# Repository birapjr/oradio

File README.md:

# oRadio
open all frequency world radio - a.k.a oRadio

oRadio is a project to create a open source radio project that anyone how has interest in radio can see how it work and be able to build his/her own from hardware building blocks.

## Parts of the project

* analog radio board (FM/MW/SW/LW/SSB)
* digital radio board (DAB/DAB+)
* sound board
* mcu board
* store board
* main board

### What is done so far

* analog radio board (FM/MW/SW/LW/SSB)

The `analog radio board (FM/MW/SW/LW/SSB)` is the board that holds the IC [Si4735](https://www.silabs.com/audio-and-radio/multiband-radios/si4734-35-radio-receivers/device.si4735) radio receiver.

Its only hold this IC so the user can make any experiments he/she wants with the IC.

Current version: `v1.0.0`

* KiCad project uses:
    - Si4735 [footprint](https://www.snapeda.com/parts/SI4735-D60-GU/Silicon%20Labs/view-part/)

* sound board

The board that connect external components to the IC Si4735 and the micro controller.

Current version: `v1.0.0`

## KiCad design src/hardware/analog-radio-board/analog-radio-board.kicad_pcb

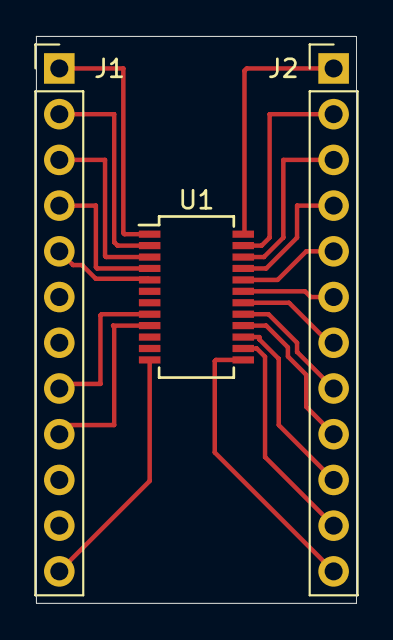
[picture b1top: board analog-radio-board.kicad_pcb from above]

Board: 2 copper layers, 17.8 x 31.5 mm, 3 parts (0 on the bottom side), 20 nets.

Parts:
J1, J2: Conn_01x12_Male; PinHeader_1x12_P2.54mm_Vertical
U1: Si4735-D60-GU; SSOP-24_3.9x8.7mm_P0.635mm

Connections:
unnamed: J1.1, U1.1
unnamed: J1.2, U1.2
unnamed: J1.3, U1.3
unnamed: J1.4, U1.4
unnamed: J1.5, U1.5
unnamed: J1.8, U1.8
unnamed: J1.9, U1.9
unnamed: J1.12, U1.12
unnamed: J2.1, U1.24
unnamed: J2.2, U1.23
unnamed: J2.3, U1.22
unnamed: J2.4, U1.21
unnamed: J2.5, U1.20
unnamed: J2.6, U1.19
unnamed: J2.7, U1.18
unnamed: J2.8, U1.17
unnamed: J2.9, U1.16
unnamed: J2.10, U1.15
unnamed: J2.11, U1.14
unnamed: J2.12, U1.13

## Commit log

2020-11-15 feat: Better README and radio-board initial data added
2020-11-17 chore: WIP
2020-11-18 feat: analog radio board v1.0.0
2020-11-27 feat: sound board initial version

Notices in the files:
src/hardware/analog-radio-board/analog-radio-board.kicad_pcb:
Designed in Berlin (c)2020
